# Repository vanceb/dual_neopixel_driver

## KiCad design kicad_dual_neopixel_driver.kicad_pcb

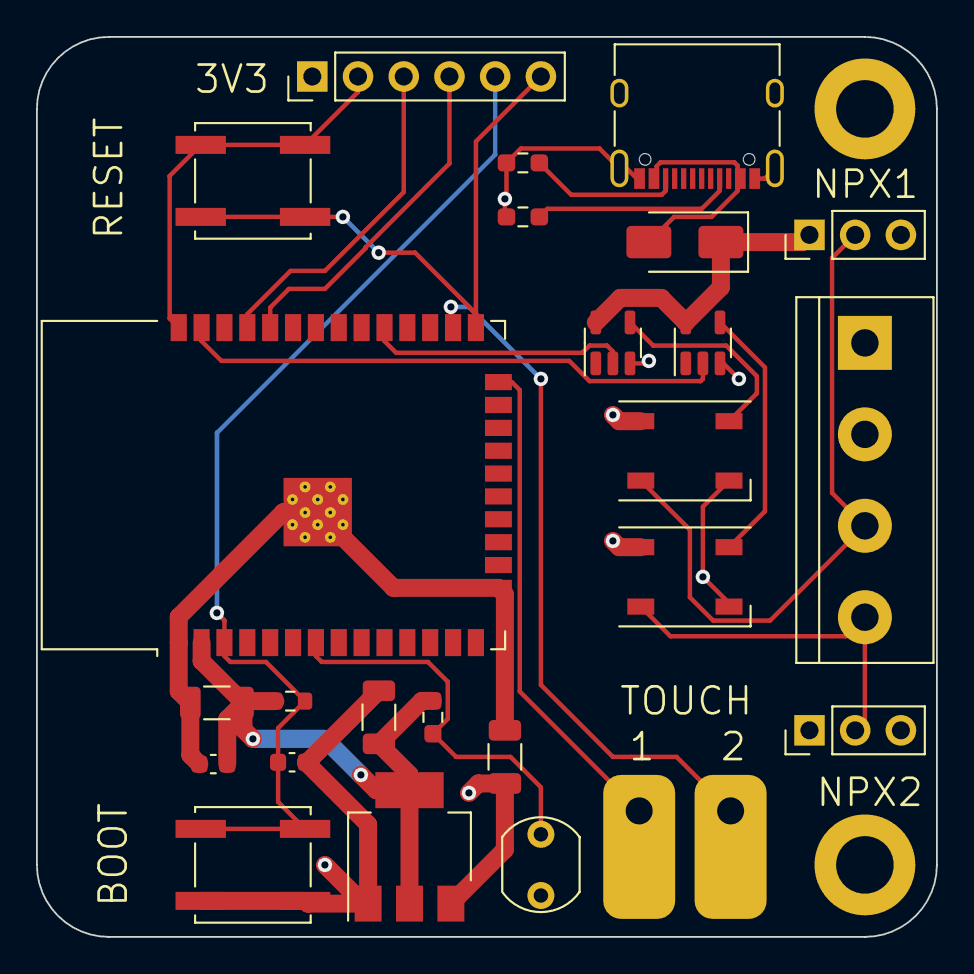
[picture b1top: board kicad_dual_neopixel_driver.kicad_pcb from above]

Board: 4 copper layers, 50.0 x 50.0 mm, 25 parts (0 on the bottom side), 19 nets.

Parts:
C1, C2, C3: 10u; C_1206_3216Metric
C4: 100n; C_0603_1608Metric
C5: 1u; C_0603_1608Metric
D1, D3: WS2812B; LED_WS2812B_PLCC4_5.0x5.0mm_P3.2mm
D2: D_Schottky; D_SMA
J1: TOUCH; 2 x 0.2 Pads
J2: NPX1; PinHeader_1x03_P2.54mm_Vertical
J3: Screw_Terminal_01x04; TerminalBlock_bornier-4_P5.08mm
J4: NPX2; PinHeader_1x03_P2.54mm_Vertical
J5: USB-C Power Only; USB-C_LCSC_C165948
J6: PROG; PinHeader_1x06_P2.54mm_Vertical
R1, R2: 5k1; R_0603_1608Metric_Pad0.98x0.95mm_HandSolder
R3: 10k; R_0603_1608Metric_Pad0.98x0.95mm_HandSolder
R4: LDR07; R_LDR_5.1x4.3mm_P3.4mm_Vertical
R5: 10k; R_0603_1608Metric
SW1: RESET; SW_Push_1P1T_NO_CK_KSC7xxJ
SW2: BOOT; SW_Push_1P1T_NO_CK_KSC7xxJ
U1: AMS1117-3.3; SOT-223-3_TabPin2
U2, U3: SN74LV1T34DBV; SOT-23-5
U4: ESP32-WROOM-32D

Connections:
+3V3: C2.1, C3.1, C4.1, J6.1, R3.1, R5.2, U1.2 (VO), U4.2 (VDD)
+5V: C1.1, D1.1 (VDD), D2.1 (K), D3.1 (VDD), J2.1, J3.1, J4.1, U1.3 (VI), U2.5 (VCC), U3.5 (VCC)
BOOT: J6.6, SW2.2, U4.25 (IO0)
GND: C1.2, C2.2, C3.2, C4.2, C5.2, D1.3 (VSS), D3.3 (VSS), J2.3, J3.2, J4.3, J5.A1 (GND), J5.A12 (GND), J5.B1 (GND), J5.B12 (GND), J5.S1 (SHIELD), J6.2, R1.2, R2.2, R4.2, SW1.1, SW2.1, U1.1 (GND), U2.3 (GND), U3.3 (GND), U4.1 (GND), U4.15 (GND), U4.38 (GND), U4.39 (GND)
LIGHT: R3.2, R4.1, U4.7 (IO35)
NPX1: U2.2 (A), U4.29 (IO5)
NPX2: U3.2 (A), U4.37 (IO23)
unnamed: D1.4 (DIN), U2.4 (Y)
unnamed: D1.2 (DOUT), J2.2, J3.3
unnamed: D2.2 (A), J5.A4 (VBUS), J5.A9 (VBUS), J5.B4 (VBUS), J5.B9 (VBUS)
unnamed: D3.4 (DIN), U3.4 (Y)
unnamed: D3.2 (DOUT), J3.4, J4.2
unnamed: J5.A5 (CC1), R2.1
unnamed: J5.B5 (CC2), R1.1
RESET: C5.1, J6.5, R5.1, SW1.2, U4.3 (EN)
RXDI_PROG: J6.4, U4.34 (RXD0/IO3)
TOUCH1: J1.1, U4.24 (IO2)
TOUCH2: J1.2, U4.26 (IO4)
TXDO_PROG: J6.3, U4.35 (TXD0/IO1)

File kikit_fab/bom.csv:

Comment,Designator,Footprint,LCSC
WS2812B,"D1,D3",LED_SMD:LED_WS2812B_PLCC4_5.0x5.0mm_P3.2mm,C2761795
AMS1117-3.3,U1,Package_TO_SOT_SMD:SOT-223-3_TabPin2,C6186
5k1,"R1,R2",Resistor_SMD:R_0603_1608Metric_Pad0.98x0.95mm_HandSolder,C23186
10u,"C1,C2,C3",Capacitor_SMD:C_1206_3216Metric,C13585
10k,R3,Resistor_SMD:R_0603_1608Metric_Pad0.98x0.95mm_HandSolder,C25804
USB-C Power Only,J5,USB-C_Power_Only:USB-C_LCSC_C165948,C165948
TOUCH,J1,Power_Pads:2 x 0.2 Pads,
SN74LV1T34DBV,"U2,U3",Package_TO_SOT_SMD:SOT-23-5,C100024
D_Schottky,D2,Diode_SMD:D_SMA,C14996
NPX1,J2,Connector_PinHeader_2.54mm:PinHeader_1x03_P2.54mm_Vertical,
LDR07,R4,OptoDevice:R_LDR_5.1x4.3mm_P3.4mm_Vertical,
NPX2,J4,Connector_PinHeader_2.54mm:PinHeader_1x03_P2.54mm_Vertical,
Screw_Terminal_01x04,J3,TerminalBlock:TerminalBlock_bornier-4_P5.08mm,
PROG,J6,Connector_PinHeader_2.54mm:PinHeader_1x06_P2.54mm_Vertical,
1u,C5,Capacitor_SMD:C_0603_1608Metric,C15849
ESP32-WROOM-32D,U4,RF_Module:ESP32-WROOM-32D,C473012
100n,C4,Capacitor_SMD:C_0603_1608Metric,C14663
BOOT,SW2,Button_Switch_SMD:SW_Push_1P1T_NO_CK_KSC7xxJ,C318884
RESET,SW1,Button_Switch_SMD:SW_Push_1P1T_NO_CK_KSC7xxJ,C318884
10k,R5,Resistor_SMD:R_0603_1608Metric,C25804
